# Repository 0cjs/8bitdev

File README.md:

8bitdev
=======

This repo is used by cjs for development of programs in 8-bit assembly
languages (for a variety of platforms) and tools to aid this development.

If you wish to discuss any of the code here, the best way to reach me is to
contact `cjs_cynic` on Telegram or `0cjs` on Discord. You can also use the
e-mail address in the commit messages, but that's more likely to get lost
in the noise of all my e-mail and will always take longer to get a response.

### Contents

- (Top Section)
  - Contents
  - Introduction
- File and Directory Organization
  - ASL (The Macroassembler AS) Notes
  - ASxxxx Notes
- Third-party Development Tools
  - VICE: The Versatile Commodore Emulator
  - MAME Multi-system Emulators
- Additional Third-party Tools
  - VICE: The Versatile Commodore Emulator
  - MAME Multi-system Emulators
- Additional Tool Information
  - Playing CMT (Cassette Tape) Images
  - The py65 Monitor

### Introduction

This repo uses [`t8dev`][] (and its dependency, `r8format`) for downloading
and building various development tools, building the code itself, unit
testing it, building ROM and disk images, and running emulators. Here we
bring it in a Git submodule `t8dev/` in order to do development on it along
with code in this repo.

Run the top-level `Test` script build everything and run all the automated
tests. This script also accepts other options; see below.

Source `t8dev/t8dev/t8setup.bash` to activate the Python virtualenv
containing `t8dev`. You can also just export $T8_PROJDIR pointing to the
root of this repo and run programs directly from `.build/virtualenv/bin/`.

This currently has been tested only under Linux (Debian 9), but is likely
to work under MacOS and other Unices. It likely can be made to work under
Windows as well, if there's demand; contact me if you're interested in
getting support for this.

File and Directory Organization
-------------------------------

Here is an overview of the major files and directories in this repo.

Files:
- `README.md`: This file.
- [`Test`](./Test): Installs third-party tools where necessary, builds the
  code and runs the unit tests. (Bash.)
- [`requirements.txt`](./requirements.txt): t8dev and other Python
  requirements to be installed in the Python virtualenv.

Directories:
- [`src/`](./src/): Assembly source code, unit tests and documentation.
  These are generally modules used by full programs under `exe/`. Most of
  the code is built with [ASL]. See [`src/README.md`](./src/README.md) in
  the subdir for more on this.
- [`exe/`](./exe/): "Top-level" assembly files for full executable program
  builds, usually just doing configuration and including code from `src/`.
  See [`exe/README`](exe/README.md) for more on this.
- [`tmp/`](./tmp/): Ignored; used to keep developer's random files out of
  the way.

Third-party Development Tools
-----------------------------

#### py65 Notes

The [PyPI `py65`][py65pypi] sometimes falls out of date. You can also
update `requirements.txt` to the current version from GitHub:

    .build/virtualenv/bin/pip install -U \
        py65@git+https://github.com/mnaberez/py65.git

This will pull the head of the main branch; to use a release branch
append `@<branch-name>` to the URL.

#### ASL (The Macroassembler AS) Notes

Versions 1.42 builds 205 through at least 218 are broken for 8bitdev due to
the "Symbols in Segment NOTHING" section disappearing from the map file.
See [`t8dev.toolset.asl`] for more details.

#### ASxxxx Notes

The Linux binaries provided for ASxxxx are 32-bit, and on 64-bit systems
will error out with "No such file or directory" when run unless the 32-bit
dynamic linker (`ld-linux.so.2`) and libraries are installed.

For this reason, by default ASxxxx is not installed and used. Use `./Test
-A` to enable assembly and testing of code using ASxxxx. This is a
persistent flag (even across fully clean `./Test -C` builds); remove
`.all-tools` from the top level repository directory to disable it.

To install the 32-bit libraries on a 64-bit Debian 9 system:

    dpkg --add-architecture i386
    apt update
    apt install libc6-i386

Additional Third-party Tools
----------------------------

The following tools do not currently have any specific support in this
repo, but can be useful for testing.

### VICE: The Versatile Commodore Emulator

[VICE] is a suite of simulators for various CBM computers, including PET
models, the VIC-20 and the Commodore 64.

### MAME Multi-system Emulators

You can install or build the latest version from `mamedev.org` or just use
your system packages; on Debian 9 they'd be installed with:

    sudo apt-get install mame mame-tools mame-doc

The documentation installed by `mame-doc`, under
<file:///usr/share/doc/mame-doc/singlehtml/index.html>, is just an older
version of what's found at <https://docs.mamedev.org>

Additional Tool Information
---------------------------

### Playing CMT (Cassette Tape) Images

See [`r8format/doc/cmtconv.md`][cmtdoc].

### The py65 Monitor

py65 includes a monitor, `py65mon`, that can be run from the command
line. With no options it drops directly into the monitor on a
simulated 6502 with 64K RAM.

Options:
- `-l FILE`: Load file at address `$0000`.
- `-r FILE`: Load ROM image at top of address space and reset into it.
- `-g ADDR`: Goto _ADDR_ after loading files.
- `-i ADDR`: Location of TTY input register `getc` (default `0xf004`)
- `-o ADDR`: Location of TTY ouput register `putc` (default `0xf001`)

Addresses given on the command line use C/Python base notation (`10`,
`0xa`, `012`) rather than the `+$` notation used with monitor
commands.

__[Command][py65-cmds] summary__ (similar to [VICE monitor][vice-mon]):

General:
- Readline command line editing available.
- Prefix numbers w/`$+%` for hex/decimal/binary. `radix` shows/sets default.
- `help [CMD]` with for more details.
- `quit`
- `add_label ADDR NAME`, `show_labels`, `delete_label NAME`: _NAME_ can be
  used in place of _ADDR_ below, and arithmetic (`start+8`) may be used.

Display and input:
- `~ NUMBER`: Displays _NUMBER_ in all bases.
- `registers`: display `PC  AC XR YR SP NV-BDIZC`.
  Set regs with `NAME=VALUE`, comma-separated.
- `mem START:END`: Display memory. Show 16-byte lines with `width 70`.
- `fill ADDR[:END] BYTE ...`: Deposit byte(s) starting at _ADDR_.
   Repeats bytes to _END_ if given.
- `disassemble START:END`
- `assemble ADDR [STMT]`: Interactive if no stmt given. Labels may be used.
- `load "FNURL" ADDR`: Load file or URL (quotes optional) at given
  address (`top` for top of memory). (Warning: C64 files will have a
  two-byte load address at the start of the file that's treated as data.)
- `save FNAME START END`

Execution:
- `reset`: Reset CPU and clear memory.
- `goto ADDR`: Set PC and resume execution
- `return`: Execute, return to monitor just before next `RTS/RTI`.
- `step`: Executes instr, disassembles next instr.
- `add_breakpoint ADDR`, `show_breakpoints`, `delete_breakpoint ADDR`.
- `cycles`: Display number of cycles since last reset.

<!-------------------------------------------------------------------->
[`t8dev.toolset.asl`]: https://github.com/mc68-net/t8dev/blob/main/t8dev/psrc/t8dev/toolset/asl.py
[`t8dev`]: https://github.com/mc68-net/t8dev
[asl]: http://john.ccac.rwth-aachen.de:8000/as/
[cmtdoc]: https://github.com/mc68-net/t8dev/blob/main/r8format/doc/cmtconv.md
[py65pypi]: https://pypi.org/project/py65/#history

[VICE]: https://vice-emu.sourceforge.io/
[py65-cmds]: https://py65.readthedocs.io/en/latest/index.html#command-reference
[py65-src]: https://github.com/mnaberez/py65
[vice-mon]: http://vice-emu.sourceforge.net/vice_12.html

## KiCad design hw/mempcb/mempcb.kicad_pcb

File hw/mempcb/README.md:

RC6502 / 50-pin Bus Reconfigurable Memory Board
===============================================

Overview
--------

This board is designed for prototyping and experimenting with JEDEC DIP-24,
DIP-28 and DIP-32 RAM, EEPROM and EPROM/PROM memory devices on the [RC6502
bus] and any system with an expansion bus connector taking a 50-pin ribbon
cable (e.g., the National/Panasonic JR-200 or some MSX computers).

The general idea is that it makes for you the common connections that will
be the same with any board: power/ground, data lines and lower address
lines. For the rest you can wire-wrap between .1" header pins bringing out
the signals from the bus connectors and sockets.

Design
------

It's a 100 mm × 100 mm board with the following:
- 39-pin RC6502 bus connector (right-angle .1" header) on one edge.
- 2×25 pin .1" header for use with a 50-pin IDC connector, for connection
  to microcomputer expansion bus connectors.
- DIP-32 footprint for a RAM socket. There is sufficient space around it to
  use a ZIF socket, though the release arm will stick out over the edge of
  the board.
- Two DIP-16 sockets for address space decode and other logic.
- Four each of Vcc, pull-up, pull-down and GND sources. (Pull-ups and
  pull-downs connect to Vcc and GND, respectively, through your choice of
  resistor value. 1 kΩ would be typical.
- A jumper to connect or disconnect the board to RC6502 bus Vcc.
- Two pad pairs at 2.50 mm pitch for connecting JST XH or similar
  connectors for supplying power to or taking power from the board.

The hardwired connections are:
- GND to the standard pins on all three sockets: pin 16 on the DIP-32 and
  pin 8 on each DIP-16.
- Vcc to the standard pins on all three sockets: pin 32 on the DIP-32 and
  pin 16 on each DIP-16. (pins 16/32 on the DIP-32, and pins 8/
- Data bus D0-D7 to the standard JEDEC pins on the DIP-32.
- Address bus A0-A10 to the standard JEDEC pins on the DIP-32.

All bus connector and IC pin signals are available on .1" headers next to
the connector/socket. These are intended to be used for wire-wrap
connections appropriate to the configuration and purpose of the board. The
connections to be made are:
- Vcc, address and control pins on the DIP-32 appropriate to the particular
  memory chip you're using. (DIP-24, DIP-28 or DIP-32, and SRAM/EEPROM or
  EPROM/PROM/ROM pin assignments.)
- Logic pins on the DIP-16s appropriate to their decoding and other
  functions. Typically a 74'138 will be used for address decoding and a
  gate package (74'00 quad NAND, 74'32 quad OR, etc.) for additional
  processing such as qualification of select and read/write lines.
- Logic and additional address pins from the RC6502 bus connector.
- All pins needed from the 2×25 microcomputer bus connector. This is left
  entirely unwired since there is no common standard for any signals on
  these expansion bus connectors.

Design and Layout Notes
-----------------------

- Though this is a two-layer board, all traces are on the back (solder)
  side, allowing the entire top (component) side to be a pseudo ground
  plane. (It's interrupted by through-holes for components and headers, but
  this should cause minimal disruption of return paths.
- It's not clear if wire-wrap will also be able to take advantage of this
  pseudo ground plane, but at least it will be no worse than wire wrap
  would normally be.
- The "power strip" around the edges of the board (on the back side) allows
  Vcc access from pretty much any point on the board without jumper wires
  or vias and topside traces. This helps preserve the pseudo ground plane.

For more on this, see Wilson Mines' [Avoiding AC-Performance Problems][wm
ac] and perhaps [Techniques for reliable high-speed digital circuits] on
forum.6502.org.

TODO
----

- Add prototype area.

<!-------------------------------------------------------------------->
[RC6502 bus]: https://github.com/tebl/RC6502-Apple-1-Replica/blob/master/Bus.md
[f65 2029]: http://forum.6502.org/viewtopic.php?f=4&t=2029
[wm ac]: https://wilsonminesco.com/6502primer/construction.html

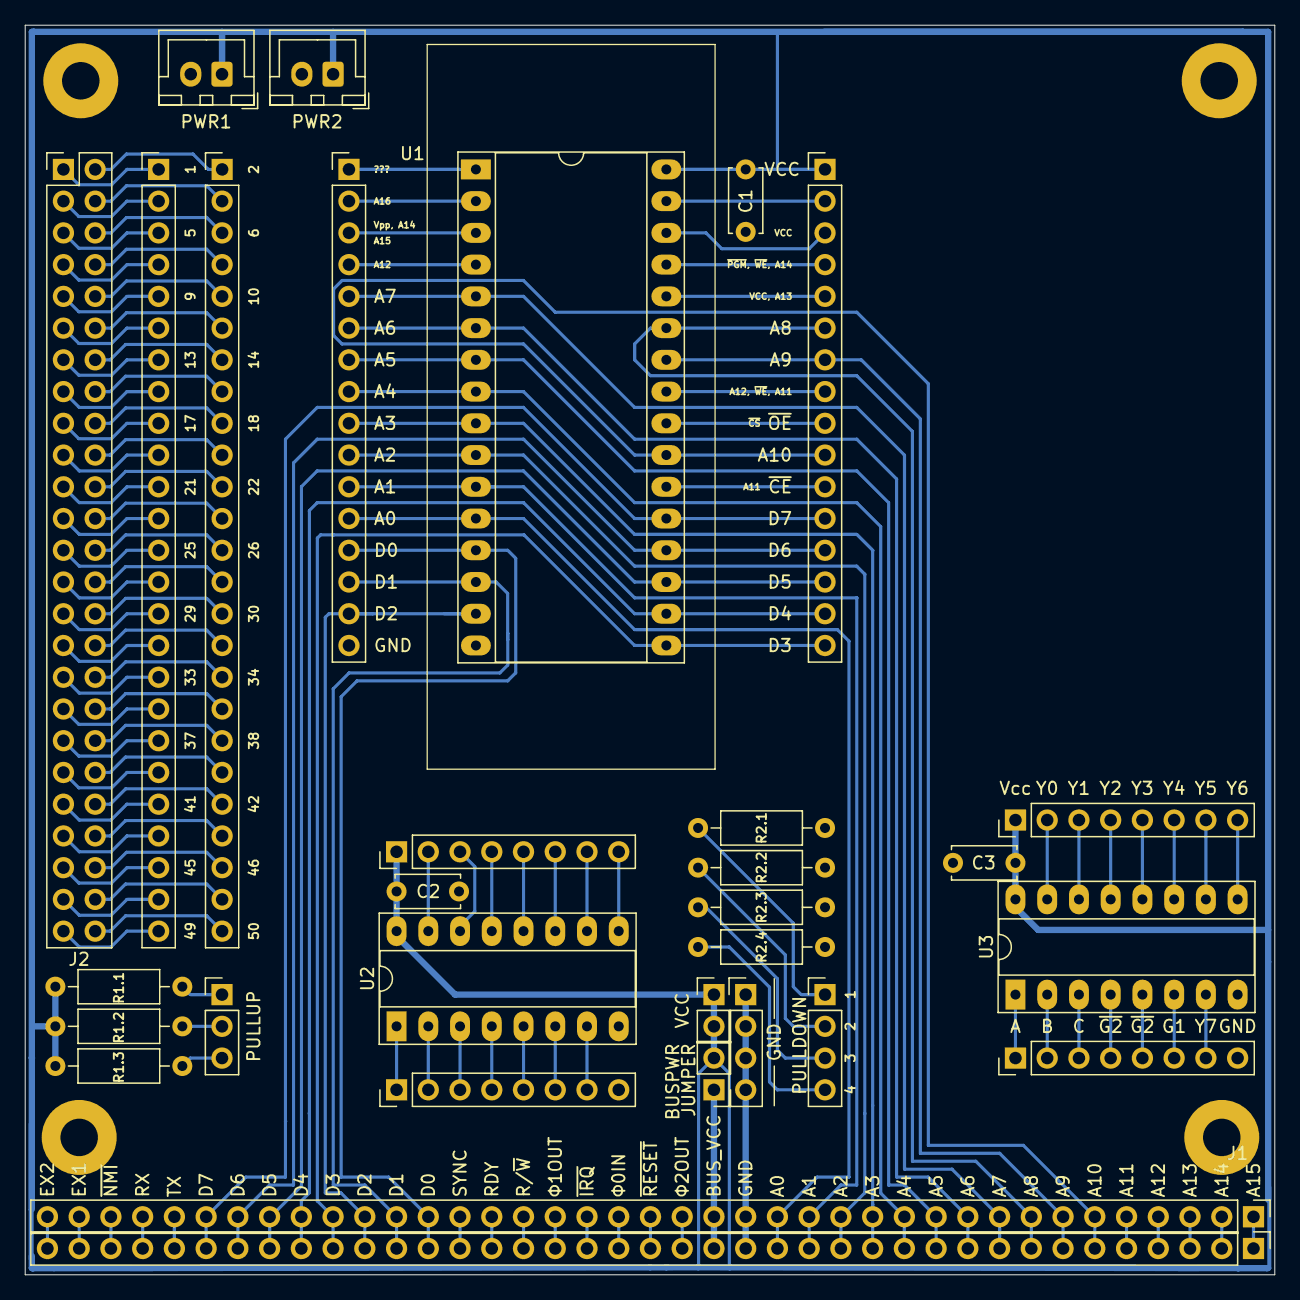
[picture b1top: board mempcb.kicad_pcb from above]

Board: 2 copper layers, 100.0 x 100.0 mm, 31 parts (0 on the bottom side), 136 nets.

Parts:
BUSPWR1: 0.1" 1x2; PinHeader_1x02_P2.54mm_Vertical
C1, C2, C3: .1μF; C_Disc_D5.0mm_W2.5mm_P5.00mm
GND1: 0.1" 1x4; PinHeader_1x04_P2.54mm_Vertical
J1: RC6502_Bus; RC6502_PinHeader_1x39_P2.54mm_Vertical
J2: 0.1" 2x25; PinHeader_2x25_P2.54mm_Vertical
PULLDOWN2: 0.1" 1x4; PinHeader_1x04_P2.54mm_Vertical
PULLUP1: 0.1" 1x3; PinHeader_1x03_P2.54mm_Vertical
PWR1, PWR2: JST-XH; JST_XH_B2B-XH-A_1x02_P2.50mm_Vertical
R1.1, R1.2, R1.3, R2.1, R2.2, R2.3, R2.4: R; R_Axial_DIN0207_L6.3mm_D2.5mm_P10.16mm_Horizontal
U1: JEDEC_DIP32_RAM; DIP-32_W15.24mm_ZIF_Socket_LongPads
U2, U3: 74LS138; DIP-16_W7.62mm_Socket_LongPads
VCC1: 0.1" 1x2; PinHeader_1x02_P2.54mm_Vertical
WW_J1: RC6502_Bus; RC6502_PinHeader_1x39_P2.54mm_Vertical
WW_J2.1, WW_J2.2: 0.1" 1x25; PinHeader_1x25_P2.54mm_Vertical
WW_U1.1, WW_U1.2: 0.1" 1x16; PinHeader_1x16_P2.54mm_Vertical
WW_U2.1, WW_U2.2, WW_U3.1, WW_U3.2: 0.1" 1x8; PinHeader_1x08_P2.54mm_Vertical

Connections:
/A0: J1.16, U1.12, WW_J1.16, WW_U1.1.12
/A1: J1.15, U1.11, WW_J1.15, WW_U1.1.11
/A2: J1.14, U1.10, WW_J1.14, WW_U1.1.10
/A3: J1.13, U1.9, WW_J1.13, WW_U1.1.9
/A4: J1.12, U1.8, WW_J1.12, WW_U1.1.8
/A5: J1.11, U1.7, WW_J1.11, WW_U1.1.7
/A6: J1.10, U1.6, WW_J1.10, WW_U1.1.6
/A7: J1.9, U1.5, WW_J1.9, WW_U1.1.5
/A8: J1.8, U1.27, WW_J1.8, WW_U1.2.6
/A9: J1.7, U1.26, WW_J1.7, WW_U1.2.7
/A10: J1.6, U1.23, WW_J1.6, WW_U1.2.10
/A11: J1.5, WW_J1.5
/A12: J1.4, WW_J1.4
/A13: J1.3, WW_J1.3
/A14: J1.2, WW_J1.2
/A15: J1.1, WW_J1.1
/BUS_VCC: BUSPWR1.1, J1.18, WW_J1.18
/D0: J1.27, U1.13, WW_J1.27, WW_U1.1.13
/D1: J1.28, U1.14, WW_J1.28, WW_U1.1.14
/D2: J1.29, U1.15, WW_J1.29, WW_U1.1.15
/D3: J1.30, U1.17, WW_J1.30, WW_U1.2.16
/D4: J1.31, U1.18, WW_J1.31, WW_U1.2.15
/D5: J1.32, U1.19, WW_J1.32, WW_U1.2.14
/D6: J1.33, U1.20, WW_J1.33, WW_U1.2.13
/D7: J1.34, U1.21, WW_J1.34, WW_U1.2.12
/EX1: J1.38, WW_J1.38
/EX2: J1.39, WW_J1.39
/GND: C1.2, C2.2, C3.2, GND1.1, GND1.2, GND1.3, GND1.4, J1.17, PWR1.2, PWR2.2, R2.1.2, R2.2.2, R2.3.2, R2.4.2, U1.16, U2.8, U3.8, WW_J1.17, WW_U1.1.16, WW_U2.1.8, WW_U3.1.8
/PHI0IN: J1.21, WW_J1.21
/PHI1OUT: J1.23, WW_J1.23
/PHI2OUT: J1.19, WW_J1.19
/RDY: J1.25, WW_J1.25
/RX: J1.36, WW_J1.36
/R_~W: J1.24, WW_J1.24
/SYNC: J1.26, WW_J1.26
/TX: J1.35, WW_J1.35
/VCC: BUSPWR1.2, C1.1, C2.1, C3.1, PWR1.1, PWR2.1, R1.1.2, R1.2.2, R1.3.2, U1.32, U2.16, U3.16, VCC1.1, VCC1.2, WW_U1.2.1, WW_U2.2.1, WW_U3.2.1
/~CE: U1.22, WW_U1.2.11
/~IRQ: J1.22, WW_J1.22
/~NMI: J1.37, WW_J1.37
/~OE: U1.24, WW_U1.2.9
/~RESET: J1.20, WW_J1.20
unnamed: J2.1, WW_J2.1.1
unnamed: J2.2, WW_J2.2.1
unnamed: J2.3, WW_J2.1.2
unnamed: J2.4, WW_J2.2.2
unnamed: J2.5, WW_J2.1.3
unnamed: J2.6, WW_J2.2.3
unnamed: J2.7, WW_J2.1.4
unnamed: J2.8, WW_J2.2.4
unnamed: J2.9, WW_J2.1.5
unnamed: J2.10, WW_J2.2.5
unnamed: J2.11, WW_J2.1.6
unnamed: J2.12, WW_J2.2.6
unnamed: J2.13, WW_J2.1.7
unnamed: J2.14, WW_J2.2.7
unnamed: J2.15, WW_J2.1.8
unnamed: J2.16, WW_J2.2.8
unnamed: J2.17, WW_J2.1.9
unnamed: J2.18, WW_J2.2.9
unnamed: J2.19, WW_J2.1.10
unnamed: J2.20, WW_J2.2.10
unnamed: J2.21, WW_J2.1.11
unnamed: J2.22, WW_J2.2.11
unnamed: J2.23, WW_J2.1.12
unnamed: J2.24, WW_J2.2.12
unnamed: J2.25, WW_J2.1.13
unnamed: J2.26, WW_J2.2.13
unnamed: J2.27, WW_J2.1.14
unnamed: J2.28, WW_J2.2.14
unnamed: J2.29, WW_J2.1.15
unnamed: J2.30, WW_J2.2.15
unnamed: J2.31, WW_J2.1.16
unnamed: J2.32, WW_J2.2.16
unnamed: J2.33, WW_J2.1.17
unnamed: J2.34, WW_J2.2.17
unnamed: J2.35, WW_J2.1.18
unnamed: J2.36, WW_J2.2.18
unnamed: J2.37, WW_J2.1.19
unnamed: J2.38, WW_J2.2.19
unnamed: J2.39, WW_J2.1.20
unnamed: J2.40, WW_J2.2.20
unnamed: J2.41, WW_J2.1.21
unnamed: J2.42, WW_J2.2.21
unnamed: J2.43, WW_J2.1.22
unnamed: J2.44, WW_J2.2.22
unnamed: J2.45, WW_J2.1.23
unnamed: J2.46, WW_J2.2.23
unnamed: J2.47, WW_J2.1.24
unnamed: J2.48, WW_J2.2.24
unnamed: J2.49, WW_J2.1.25
unnamed: J2.50, WW_J2.2.25
unnamed: PULLDOWN2.1, R2.1.1
unnamed: PULLDOWN2.2, R2.2.1
unnamed: PULLDOWN2.3, R2.3.1
unnamed: PULLDOWN2.4, R2.4.1
unnamed: PULLUP1.1, R1.1.1
unnamed: PULLUP1.2, R1.2.1
unnamed: PULLUP1.3, R1.3.1
unnamed: U1.1, WW_U1.1.1
unnamed: U1.2, WW_U1.1.2
unnamed: U1.3, WW_U1.1.3
unnamed: U1.4, WW_U1.1.4
unnamed: U1.25, WW_U1.2.8
unnamed: U1.28, WW_U1.2.5
unnamed: U1.29, WW_U1.2.4
unnamed: U1.30, WW_U1.2.3
unnamed: U1.31, WW_U1.2.2
unnamed: U2.1, WW_U2.1.1
unnamed: U2.2, WW_U2.1.2
unnamed: U2.3, WW_U2.1.3
unnamed: U2.4, WW_U2.1.4
unnamed: U2.5, WW_U2.1.5
unnamed: U2.6, WW_U2.1.6
unnamed: U2.7, WW_U2.1.7
unnamed: U2.9, WW_U2.2.8
unnamed: U2.10, WW_U2.2.7
unnamed: U2.11, WW_U2.2.6
unnamed: U2.12, WW_U2.2.5
unnamed: U2.13, WW_U2.2.4
unnamed: U2.14, WW_U2.2.3
unnamed: U2.15, WW_U2.2.2
unnamed: U3.1, WW_U3.1.1
unnamed: U3.2, WW_U3.1.2
unnamed: U3.3, WW_U3.1.3
unnamed: U3.4, WW_U3.1.4
unnamed: U3.5, WW_U3.1.5
unnamed: U3.6, WW_U3.1.6
unnamed: U3.7, WW_U3.1.7
unnamed: U3.9, WW_U3.2.8
unnamed: U3.10, WW_U3.2.7
unnamed: U3.11, WW_U3.2.6
unnamed: U3.12, WW_U3.2.5
unnamed: U3.13, WW_U3.2.4
unnamed: U3.14, WW_U3.2.3
unnamed: U3.15, WW_U3.2.2

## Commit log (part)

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2024-11-10 i8080/prvischar/config: Don't print attribute off code if no attributes on
    This adds 8 bytes to the code (56 → 64 bytes). That's annoying, given that
    this is used in the space-constrained TMON, but not as annoying as a lot of
    unnecessary terminal codes being printed when the terminal strings are
    incorrect.
2024-11-12 src/stdtest*: Remove `dup` functionality from dbtest
    The "duplicate this byte N times" syntax is different for Motorola
    `byt` and Intel `db` operands, so even though we can redefine `byt` to
    `db`, the syntax is still not entirely compatible. We're working
    on ways to deal with thus, but so far a straight function substitution
    doesn't work because that works on values, not at the text level.
    In the meantime, we just remove the test for `[3]$FF` because we
2024-11-14 i8080/tmon.pt: Add tests for byte deposit mode, exposing bug
    It turns out that in byte deposit mode with advance-to-next turned on,
    starting a deposit and entering just CR still moves the deposit start
    forward. For the moment we've xfailed this test.
    This involved some refactoring of test_deposit_ascii() to allow it to test
    byte and word deposit modes; thus it's renamed to test_deposit(), and the
    other test_deposit_*() functions that were actually testing the settings
2024-11-14 tmon/TODO: Another bug (or bugs!) related to exec routines
2024-11-21 88: Easier way to run progs in this repo, and not using a shell function
    (Shell functions often don't work when passed to programs that interpret
    your command lines.)
2024-11-22 Test,exe/nec/pc8001/hello: Run CSCP NEC emulator with expansion ROM
    If the -E parameter is exe/nec/, we run a CSCP emulator with the name
    taken from the next component down in the directory structure.
    Currently we hard-code this to patching N80.ROM at $6000, which is
    the expansion ROM area on the PC-8001; we'll have to expand the
    processing of this for other machines.
    We also need to look into how we might use other data setup methods,
2024-11-22 exe//pc8001/hellorom: Demonstrate where we find the CMD arguments
    We print HL, DE, BC, and drop to the monitor, where we can dump
    memory to show that HL points to the start of the remainder of
    the command line, after cleanup.
2024-11-26 exe//m100/cotest: Better comment for MAXRAM
2024-11-28 Test,exe/kc85/*: Use new r8format `p2b` program to generate KC85 .CO files
    Our COTEST.CO program still uses the old "define it in the assembly"
    method, so as to document that, but HELLO.CO is now generated using p2b,
    which is a new program on the branch of r8format that we also move to with
    this commit.
2024-11-30 i8080/prvischar/loctl: When "low" control chars only need be made visible
    This is actually all control characters in the lower-half of an 8-bit
    range, including not just $00-$1F, but also $7F (DEL). This is typically
    used when all characters from $80-$FF are printable.
2024-11-30 exe//tk85/portmon: Print data returned from `readbyte` routine
2024-12-05 z80/wbw2048: "2048" ROM game from RomWBW
    This is a straight copy of `Source/HBIOS/game.asm`[1]
    from RomWBW[2] commit 56a1e867. (And that in turns is
    a port of [3]; perhaps we should be using that instead.)
    [1]: https://github.com/wwarthen/RomWBW/blob/master/Source/HBIOS/game.asm
    [2]: https://github.com/wwarthen/RomWBW.git
    [3]: https://github.com/maccasoft/z80-apps/blob/master/2048.ASM
2024-12-05 i8080/tmon: Disable pushv/popv check for symbols
    This doesn't work when we bring in tmon in a section … endsection block. We
    should just change this to generate error messages in some nice way. Maybe
    we can set up a std.i80 macro that tests a symbol and generates an error if
    it's not defined.
2024-12-14 Test: More failing builds are `fail`, not internal error
2024-12-14 exe/pc8001/exprom1: Replace CMD HI with CMD HELP
2024-12-15 i8080/tmon: Int entry char now `^`; add regular entry char `.`
    This is the character that preceeds the register dump done on entry.
    Originally, it was just to be an indication that we'd entered the monitor
    via the interrupt entry point (and thus have a PC to continue at), but it
    turns out to be useful to help separate any program output from the
    monitor's register dump, too.
    So we give the regular entry point a preceding `.`, and change the
2025-01-23 src/tmon/TODO: `d` command executed directly from `e` params entry
2025-01-26 requirements.txt: Remove `== 0.2.*` from t8dev
    This doesn't actually seem to have been doing anything, since the version
    in the submodule commit we're using is `0.3.0.dev12`. Weird, but we
    definitely want to be using whatever's pinned for the submodule.
2025-02-03 src/tmon/PLATFORM: Notes for PC-8001 and a few general platform notes
2025-02-16 src/conftest → conftest: Move all conftest code to top-level file
    This moves the `from testmc.pytest import *` from src/conftest.py to
    conftest.py, since it does no harm to include that at the top level rather
    than just for code under src/. This enables us to remove src/conftest.py,
    having all our configuration now in just the one conftest.py file at the
    top level.
2025-02-28 src/i8080/tmon: Add `t` parameter to `q`uit command
    This will allow us to quit "to" different programs, such as BASIC
    vs built-in monitor.
2025-03-03 exe//pc8001/README: ROM/EPROM hardware
2025-03-05 src//tmon.i80: Print an `@` before the prompt when we re-init param vals
    It's useful to know that our param vals have been stomped on by
    something when we re-enter the monitor.
2025-03-09 src/i8080/tmon: Test user notification (`@`) of param re-init
    t8dev updated to 0.3.0.dev1 for new `MBytesIO` API functions that
    make testing this easier and more clear.
2025-03-11 src/i8080//crc_16_ccitt: Clarify XOR instructions
    Explicitly add the implicit A target register to the XOR instructions
    because that just makes it easier to see that it's operating on two
    registers or a register and a value.
2025-03-18 src/mc68//crc_16_ccitt: CRC-16-CCITT (x¹⁶+x¹²+x⁵+1) as used by Xmodem, etc.
    The unit tests for this are a modified copy of the ones substantially
    similar to those for the 8080 version, except:
    1. Different call convention for the parameters; and
    2. Better debugging output for failures.
2025-03-28 src/*/qhex.pt: Get `R` from fixure instead of explicit Machine.Registers
    Fixtures can of course use other fixtures, and we
    take advantage of that here.
2025-03-28 README: Update to roughly match current state of repo
    This mostly removes things that are now separated out into t8dev
    and r8format and points to them.
2025-04-09 t8dev/: Update to main head 1d8c3fa
2025-04-21 Test: Also assemble .z80 files under exe/
2025-04-25 src/i85/prstr: Generic prstr and prnl routines for platforms without them
    These are generated only if `prstr` and `prnl`, respectively, are not
    already defined, so that we don't have extra code (and a duplicate
    symbol!) if they're already defined via calls to the platfrom BIOS or
    whatever.
    This changes several exe/* programs now to include i8080/prstr.i80
    rather than have their own custom definitions of prstr and/or prnl.
2025-04-27 t8dev: main branch 9efb821 for better error messages from runasl()
2025-04-27 src/jr200/biosdef: prstr0b → prstrQ
    This prints 0-terminated strings, so we no longer need the 0 in the
    name, per the last commit.
    Make it more clear with a trailing `Q` that this prints only if
    "quiet" mode is not set. I don't recall why I thought that a trailing
    `b` was a clear way to state this.
2025-04-29 Test: Now just one t8dev submodule that contains t8dev+r8format
2025-05-03 t8dev: head of `main` 8c55556 for Sharp MZ-80K ROM configurations
2025-05-05 t8dev,Test: main 1a05afe for cmtconv, CSCP emulator updates
    - cmtconv now automatically detects the input format (changed from `obj`
    to `asl`) when given a `*.p` file.
    - CSCP now has an MZ-80K ROM config
2025-05-05 WIP i8080/clic/qexpr: Start working out parser interface
    XXX We need a bunch of work on the HeapBuilder test class for this
    to separate producing object values from depositing them in memory.
2025-05-08 exe/cpm/tmonlo: Fix checks for stomping on other code/data
    The check to see if we were stomping on tmon code was wrong; we needed
    to check that the initialisation code doesn't cross into tmon_rom, not
    tmon_ram. (We don't care if it overlaps tmon_ram, since that will be
    re-initialised after the init code has run anyway.)
    Add another check to ensure that prvattr_* is not overlapping tmon_ram,
    becuase if the tmon_ram init/usage stomps on prvattr_* then our terminal
2025-06-02 t8dev/: Update to `main` c587898 (cmpasl fixes, mainly)
2025-06-02 exe/kc85/m100/tmon: Fix test for workspace overflow into stack
    When we changed from having the stack always below the work area to
    having it independent, and moved the stack to the top of meory (above
    the work area), we didn't change the tests that checked for overflow
    (over-allocation) of those areas. Fix this so we now define a minimum
    stacksize and check that tmon_ram, below it, doesn't extend into that
    minimum stack size. Also fix some broken comments related to this.
2025-06-14 t8dev/: `main` commit 50cac86
2025-06-15 i8080/tmon qhexdigitDE: Set carry to indicate error status, preserve B
    Though not needed by `qhex`, future callers will need to be able to
    check to see if a valid digit was read or not since they will want to
    read fixed number of valid digits, rather than as many as the user
    cares to type. Adds one byte to code size.
    We now preserve B, as well as C and HL, which we also believe will
    help future callers. Adds two bytes to code size.
2025-07-14 tmon/test.py: Extract log_interaction() from test_calc()
    This handles a bunch of work common to a lot of tests, though we do
    not yet have the additional tests that will also use this.
2025-07-15 exe/tmc/i8080/tmon: Move entry/exit code much further away from stack
    When we changed from tmon_stksz to tmon_stack it re-ordered things and
    we moved the stack at $200. Unfortunately, this gave us only a dozen
    bytes of stack before starting to overwrite the tmc init/exit code.
    This just barely worked with the current version of tmon, but caused
    the exit code to be overwritten in development versions, so that
    entering data with `,` caused the `q` command to fail. (Unless you set
2025-07-16 i8080/tmon: Replace `ld a,0` with `xor a,a`
    This saves a byte.
    Add a comment on another `ld a,0` explaining why we can't replace
    that one with `xor a,a`.
2025-07-16 i8080/tmon test_prompt_cancel: Move to tmon/test.py test_cancel
    This removes the need to have a local label in `cancel` and
    makes this test generic to all platforms.
    NAK and CAN constants also move up to tmon/test.py.
2025-07-17 i8080/selasmtest: Show how to make this idea work (kinda)
    It relies on the developer to make sure that there's always a use
    before the library file is included.
2025-07-18 i8080/tmon cmd_memcopy: smaller/easier way of calculating length
    The `subHLpBC` routine existed only because we needed to calculate the
    length without using DE (and so could not use `subHLDE`), but we can
    do that calculation before we load DE with the target address, letting
    us re-use `subHLDE` and drop `subHLpBC`.
    13 bytes saved.
2025-07-22 i8080/arith cpBCHL: set zero flag as well as carry
    Also check that BC and HL are not modified
2025-07-22 i8080/clic/prexpr: Print true as just 't' instead of '#t'
    Scheme uses the '#' prefix for special values, but we don't really
    do that, and don't want people to think that there's a '#f', do
    instead just use the Common Lisp form, a bare 't'. (This also
    better matches 'nil'.
2025-07-24 clic/library: Note on "tiny" lib problems; eq? etc.; rename `md` to `mw`
2025-07-24 WIP i8080/clic/qform: A very basic rtok
    It doesn't do length checks, much less escape characters.
2025-07-25 WIP src/i8080/heap hcons: Initial simple allocation routine
2025-07-25 exe//sd-sbc200/: Build "hello" program
    The BIOS had to be split into two separate files: bios.inc with the
    definitions and bioscode.inc with the generated code. This is because
    the reset macro must be defined before it's used, but the serial I/O
    code can't be at the start because you need to start with the reset
    macro.
    Build .bin files for both hello and serial-echo; the latter lets us
2025-08-03 WIP exe/sbc/sd-sbc200/tmon.z80: tmon monitor and a small BIOS
    ROM_BASE is $E000; RAM use is $FF00-$FFFF, which works with three
    different ROM size configurations. See PLATFORM.md and exe//README.md
    for details on this.
    Test includes the exe//README.md in the release because we reference
    it from PLATFORM.md. (The memory config is too complex to go into all
    the details in PLATFORM.md,)
2025-08-03 src/tmon/README: Use ° symbol to mark single-key (0-arg) commands
    We were already using ° for the main command descriptions, but the
    input procedures section and the command summary table were using ¹.
    We choose to go with ° because it's stands out slightly more and
    doesn't conflict with the use of superscript numbers in, e.g., the
    CRC polynomal description.
2025-08-06 mos65/pr/str prstr: Demo a version that works w/prchar destroying Y
    This is not something we need, but something someone asked about in
    a forum. It actually serves as a pretty good demonstration of why
    prchar should preserve all registers.
    This code isn't particularly clever, needing two loads even, but still
    preserves X.
2025-08-12 t8dev: Latest `main` b98942b: just formatting etc.
2025-09-07 mos65/pr/str prstr: Clarify comments, including that prchar must ♡XY
